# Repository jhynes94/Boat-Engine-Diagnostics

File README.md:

# Boat-Engine-Diagnostics
Fun project to get started

## To Develop With

Download and add the following library to KiCAD
https://github.com/Digi-Key/digikey-kicad-library

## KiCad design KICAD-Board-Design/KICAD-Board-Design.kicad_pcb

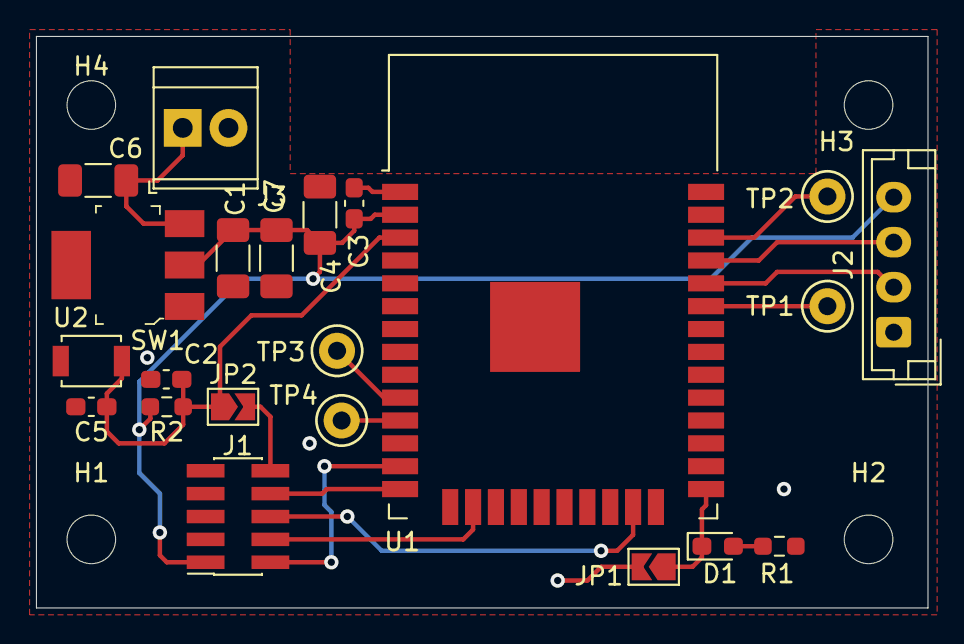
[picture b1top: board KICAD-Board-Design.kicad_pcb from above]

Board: 2 copper layers, 49.5 x 31.8 mm, 26 parts (0 on the bottom side), 17 nets.

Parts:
C1, C6: 10uF; C_1206_3216Metric_Pad1.33x1.80mm_HandSolder
C2: 1uF; C_0603_1608Metric_Pad1.08x0.95mm_HandSolder
C3, C5: 0.1uF; C_0603_1608Metric_Pad1.08x0.95mm_HandSolder
C4, C7: 22uF; C_1206_3216Metric_Pad1.33x1.80mm_HandSolder
D1: LED; LED_0603_1608Metric_Pad1.05x0.95mm_HandSolder
H1, H2, H3, H4: MountingHole; MountingHole_2.7mm_M2.5
J1: Conn_ARM_JTAG_SWD_10; ARM Cortex JTAG SWD 10pin Connector
J2: Conn_01x04; JST_EH_B4B-EH-A_1x04_P2.50mm_Vertical
J3: Conn_01x02; TerminalBlock_TE_282834-2_1x02_P2.54mm_Horizontal
JP1, JP2: Jumper_NO_Small; SolderJumper-2_P1.3mm_Open_TrianglePad1.0x1.5mm
R1: 68; R_0603_1608Metric_Pad0.98x0.95mm_HandSolder
R2: 10K; R_0603_1608Metric_Pad0.98x0.95mm_HandSolder
SW1: SW_Push; SW_SPST_B3U-1000P
TP1, TP2, TP3, TP4: TestPoint; TestPoint_Keystone_5000-5004_Miniature
U1: ESP32-WROOM-32D; ESP32-WROOM-32
U2: AZ1117CH-3_3TRG1; SOT-223

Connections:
+3V3: C1.1, C3.1, C4.1, C7.1, J1.1, J2.1, R2.1, U1.2, U2.2
+12V: C6.1, J3.1, U2.3
/ADC2_CH8: TP3.1, U1.10
/ADC2_CH9: TP4.1, U1.11
/I2C_SCL: TP2.1, U1.36
/I2C_SDA: TP1.1, U1.33
/JTAG_TCK: J1.4, U1.16
/JTAG_TDI: J1.8, U1.14
/JTAG_TDO: J1.6, U1.23
/JTAG_TMS: J1.2, U1.13
/UART_RX: J2.3, U1.34
/UART_TX: J2.2, U1.35
/nReset: J1.10, JP2.2
GND: C1.2, C2.2, C3.2, C4.2, C5.1, C6.2, C7.2, J1.3, J1.5, J1.9, J2.4, J3.2, JP1.2, R1.2, SW1.1, U1.1, U1.15, U1.38, U1.39, U2.1
unnamed: C2.1, C5.2, JP2.1, R2.2, SW1.2, U1.3
unnamed: D1.1, JP1.1, U1.25
unnamed: D1.2, R1.1

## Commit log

2020-12-12 updated .gitignore for KICAD and Arduino
2020-12-12 Created initial Project
2020-12-12 Added Power ports
2020-12-12 Added ESP32 and JTAG connector
2020-12-13 Added Perf components
2021-01-03 Beginnging Layout
2021-01-04 Layout Complete
